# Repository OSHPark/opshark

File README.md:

# LAN'd Shark Project
The LAN'd Shark is a small, wifi-connected shark robot with some wicked hair and underglow lights. This was built and designed by the Oshpark team for [PDX Mini-Maker Faire](https://www.omsi.edu/maker-faire-pdx) 2015. 

The shark communicates via an MQTT server, and has supplimental remote control boards that allow a direct interface. However, you could esily modify it for automated or automatic control. If you need a remote MQTT server, [data.sparkfun.com](https://data.sparkfun.com/) is simple and easy to use, or you can install your own with tools  such as [Mosquitto](http://mosquitto.org/).

## Project Status
### [BaseStation](basestation/)
The basestation is fully operational, and capable of reading up to 3 teensies, and transmitting data over a network to an MQTT server.

### [Controller](controller/)
The controller is fully operational in both hardware and code.

### [Shark Bot](sharkbot/)
The Shark Brains hardware is fully operational, and can drive several servo motors from an ESP2866. 

The chassis mechanics are still a bit undefined, and a bit erratic. However, the base board works great as a mounting platform for servo motors, and can be laser cut

The Arduino sketch is still in a bit of a mess, but can read incoming controller data and react. However, the Animation and ServoPlus libraries have some bugs and needs to be rewritten/updated in order for the shark to react correctly.

Here's a picture of the completed Sharkbot. 

# Required Utilities
## Software
[Arduino 1.65](https://www.arduino.cc/en/Main/Software) 

[TeensyDuino](https://www.pjrc.com/teensy/td_download.html) if using the controllers

[ESP2866 Arduino](https://github.com/esp8266/Arduino) For the Sharkbot and basestation boards

[Eagle CAD](http://www.cadsoftusa.com/download-eagle/) is needed to modify the PCB files or generate gerbers. The `.BRD` files can be directly to [OSHPark.com](http://oshpark.com) for purchase without Eagle.

## Arduino Libraries
[PubSub Client](https://github.com/Imroy/pubsubclient)

[Teensy 3.1 SPI Slave library](https://github.com/soerup/Teensy-3.0-SPI-Master---Slave) for the controller boards

[Adafruit Neopixel (Teensy version)](https://github.com/PaulStoffregen/Adafruit_NeoPixel)

# Liscence 
Released currently under the [MIT License](./LICENSE.txt)

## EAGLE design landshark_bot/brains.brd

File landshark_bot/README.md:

# Shark Chassis
This set of boards houses the roving LAN'd Sharks, complete with an ESP8266-12E board for a controller. 

# Software
This code uses the [ESP8266 Arduino](https://github.com/esp8266/Arduino) platform for the codebase. It also uses the Adafruit Neopixel library, which is conveniently included with the ESP Arduino downloads.

# Hardware

A very helpful resource was this tutorial for [creating a shark in maya](http://cgi.tutsplus.com/tutorials/create-a-realistic-shark-in-maya-using-subdivision-surfaces-part-3--cg-31246), even though I only used the 2d outline.

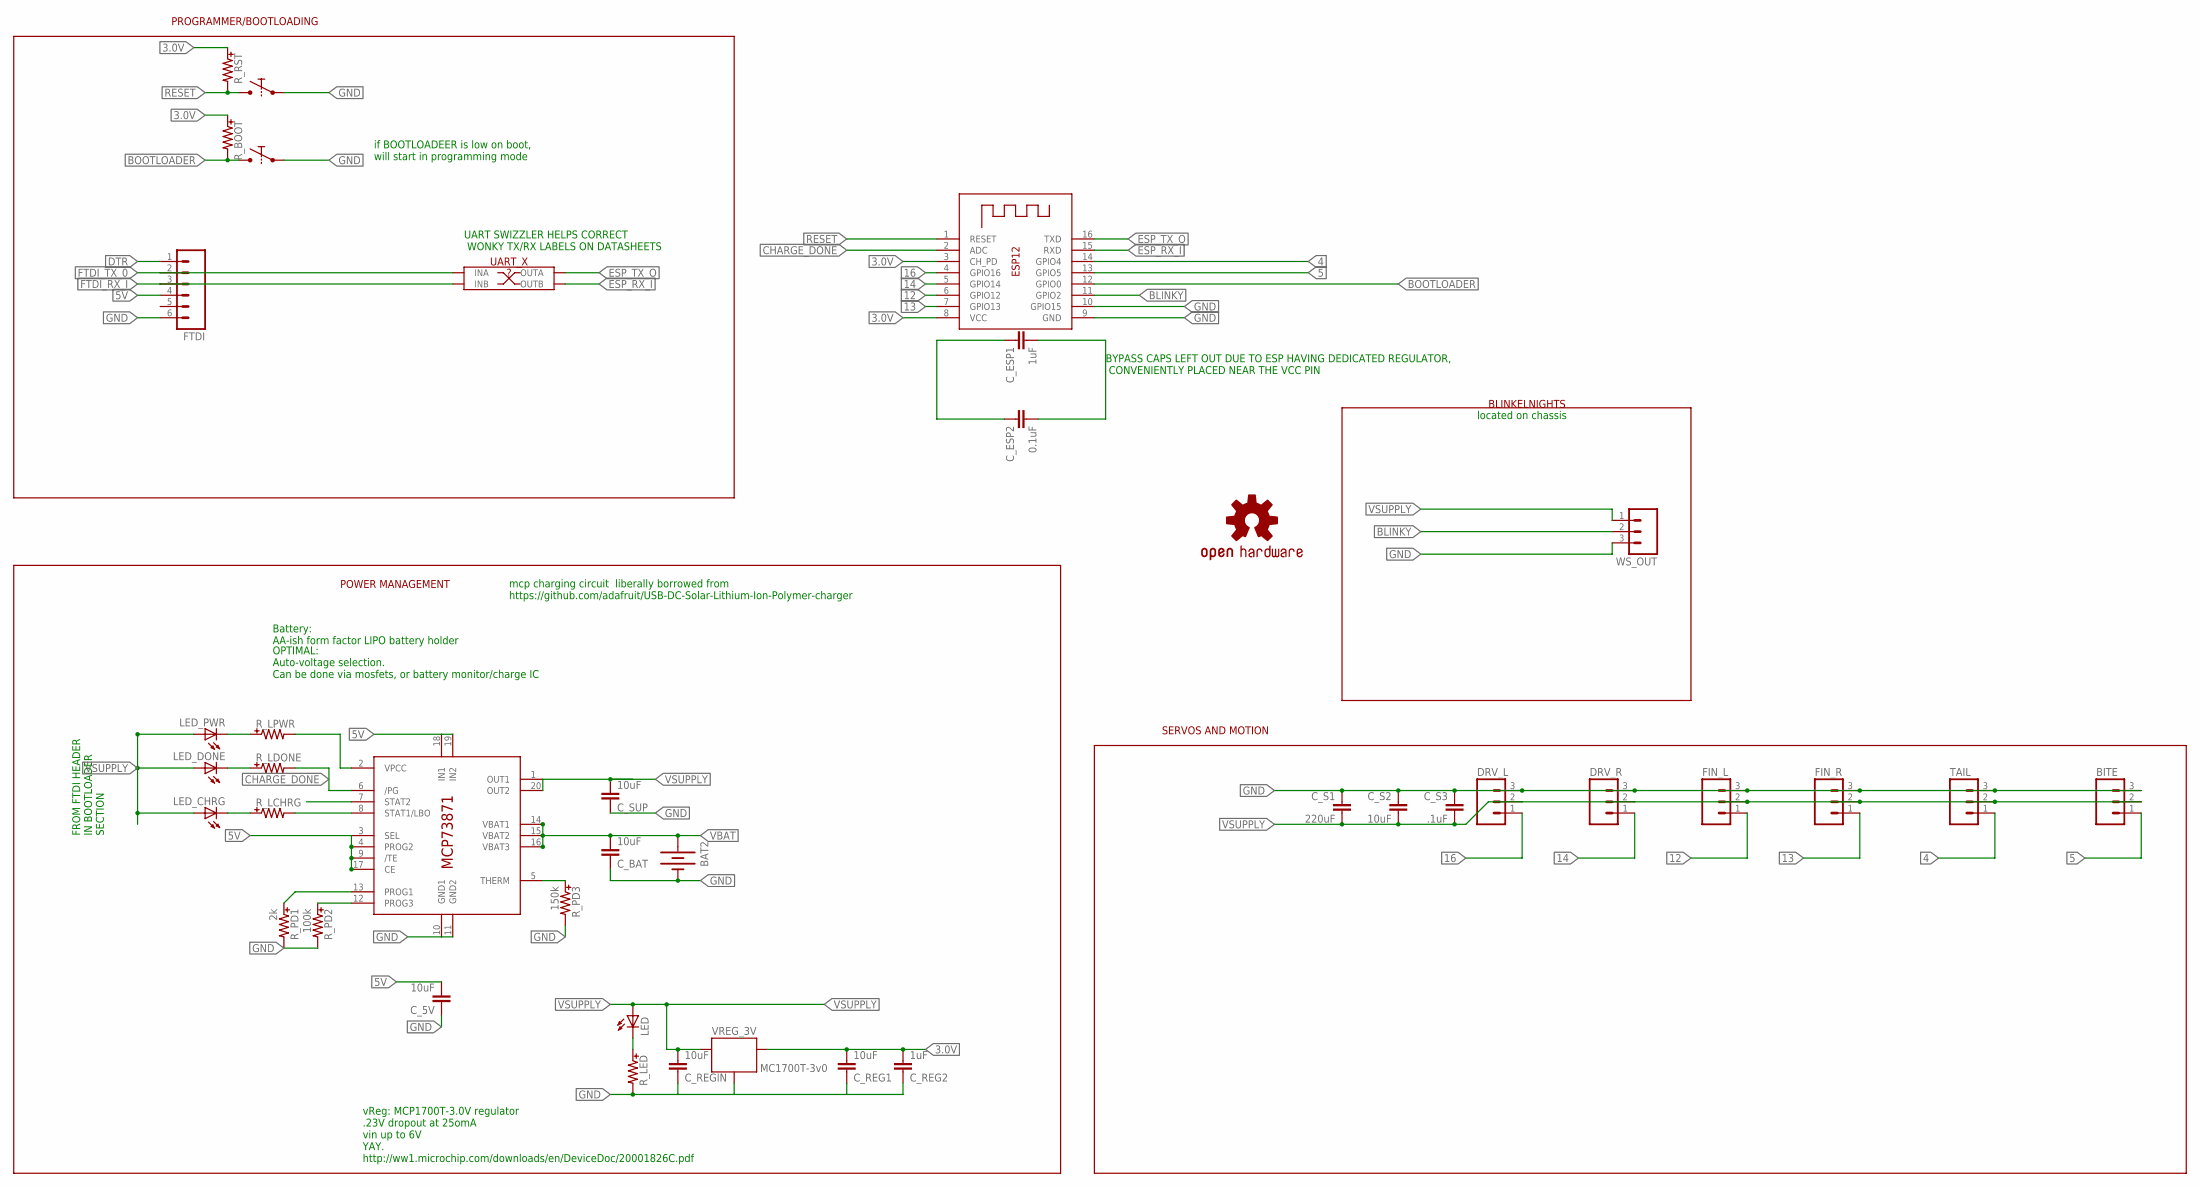
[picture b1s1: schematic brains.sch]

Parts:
BAT2: BATTERYAA; BATTERY-AA
BITE: M03LOCK; 1X03_LOCK
BTN_PROG: BUTTONPJRC; BUTTON-PJRC
BTN_RST: BUTTONPJRC; BUTTON-PJRC
C_5V: 10uF; 0402-0603-0805-UNIVERSAL
C_BAT: 10uF; 0402-0603-0805-UNIVERSAL
C_ESP1: 1uF; 0402-0603-0805-UNIVERSAL
C_ESP2: 0.1uF; 0402-0603-0805-UNIVERSAL
C_REG1: 10uF; 0402-0603-0805-UNIVERSAL
C_REG2: 1uF; 0402-0603-0805-UNIVERSAL
C_REGIN: 10uF; 0402-0603-0805-UNIVERSAL
C_S1: 220uF; 1210
C_S2: 10uF; 0402-0603-0805-UNIVERSAL
C_S3: .1uF; 0402-0603-0805-UNIVERSAL
C_SUP: 10uF; 0402-0603-0805-UNIVERSAL
DRV_L: M03LOCK; 1X03_LOCK
DRV_R: M03LOCK; 1X03_LOCK
FIN_L: M03LOCK; 1X03_LOCK
FIN_R: M03LOCK; 1X03_LOCK
FTDI: M06LOCK; 1X06_LOCK
IC_LIPO: MCP73871; QFN20
LED: LEDUNIVERSAL; 0402-0603-0805-UNIVERSAL
LED_CHRG: LEDUNIVERSAL; 0402-0603-0805-UNIVERSAL
LED_DONE: LEDUNIVERSAL; 0402-0603-0805-UNIVERSAL
LED_PWR: LEDUNIVERSAL; 0402-0603-0805-UNIVERSAL
LOGO1: OSHW-LOGOS; OSHW-LOGO-S
R_BOOT: RESISTORUNIVERSAL; 0402-0603-0805-UNIVERSAL
R_LCHRG: RESISTORUNIVERSAL; 0402-0603-0805-UNIVERSAL
R_LDONE: RESISTORUNIVERSAL; 0402-0603-0805-UNIVERSAL
R_LED: RESISTORUNIVERSAL; 0402-0603-0805-UNIVERSAL
R_LPWR: RESISTORUNIVERSAL; 0402-0603-0805-UNIVERSAL
R_PD1: 2k; 0402-0603-0805-UNIVERSAL
R_PD2: 100k; 0402-0603-0805-UNIVERSAL
R_PD3: 150k; 0402-0603-0805-UNIVERSAL
R_RST: RESISTORUNIVERSAL; 0402-0603-0805-UNIVERSAL
TAIL: M03LOCK; 1X03_LOCK
UART_X: UART_SWITCHER0603; UART_SWITCHER_0603
VREG_3V: MC1700T-3v0; SOT23
WS_OUT: M03LOCK; 1X03_LOCK
X1: ESP-12

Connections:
3.0V: C_REG1.+ (2), C_REG2.+ (2), R_BOOT.+ (1), R_RST.+ (1), VREG_3V.2 (OUT), X1.3 (CH_PD), X1.8 (VCC)
4: TAIL.1, X1.14 (GPIO4)
5: BITE.1, X1.13 (GPIO5)
5V: C_5V.+ (2), FTDI.4, IC_LIPO.3 (SEL), IC_LIPO.4 (PROG2), IC_LIPO.9 (/TE), IC_LIPO.17 (CE), IC_LIPO.18 (IN1), IC_LIPO.19 (IN2)
12: FIN_L.1, X1.6 (GPIO12)
13: FIN_R.1, X1.7 (GPIO13)
14: DRV_R.1, X1.5 (GPIO14)
16: DRV_L.1, X1.4 (GPIO16)
BLINKY: WS_OUT.2, X1.11 (GPIO2)
BOOTLOADER: BTN_PROG.A1, BTN_PROG.A2, R_BOOT.- (2), X1.12 (GPIO0)
CHARGE_DONE: IC_LIPO.6 (/PG), R_LDONE.- (2), X1.2 (ADC)
DTR: FTDI.1
ESP_RX_I: UART_X.TX_B (OUTB), X1.15 (RXD)
ESP_TX_O: UART_X.RX_B (OUTA), X1.16 (TXD)
FTDI_RX_I: FTDI.3, UART_X.RX_A (INB)
FTDI_TX_0: FTDI.2, UART_X.TX_A (INA)
GND: BAT2.GND@1 (-), BITE.3, BTN_PROG.B1, BTN_PROG.B2, BTN_RST.B1, BTN_RST.B2, C_5V.- (1), C_BAT.- (1), C_REG1.- (1), C_REG2.- (1), C_REGIN.- (1), C_S1.1, C_S2.- (1), C_S3.- (1), C_SUP.- (1), DRV_L.3, DRV_R.3, FIN_L.3, FIN_R.3, FTDI.6, IC_LIPO.10 (GND1), IC_LIPO.11 (GND2), R_LED.- (2), R_PD1.- (2), R_PD2.- (2), R_PD3.- (2), TAIL.3, VREG_3V.1 (GND), WS_OUT.3, X1.9 (GND), X1.10 (GPIO15)
unnamed: IC_LIPO.8 (STAT1/LBO), R_LCHRG.- (2)
unnamed: C_ESP1.- (1), C_ESP2.- (1)
unnamed: IC_LIPO.5 (THERM), R_PD3.+ (1)
unnamed: LED_CHRG.- (C), R_LCHRG.+ (1)
unnamed: LED.- (C), R_LED.+ (1)
unnamed: LED_DONE.- (C), R_LDONE.+ (1)
unnamed: LED_PWR.- (C), R_LPWR.+ (1)
unnamed: IC_LIPO.2 (VPCC), R_LPWR.- (2)
unnamed: C_ESP1.+ (2), C_ESP2.+ (2)
unnamed: IC_LIPO.12 (PROG3), R_PD2.+ (1)
unnamed: IC_LIPO.13 (PROG1), R_PD1.+ (1)
RESET: BTN_RST.A1, BTN_RST.A2, R_RST.- (2), X1.1 (RESET)
VBAT: BAT2.PWR@1 (+), C_BAT.+ (2), IC_LIPO.14 (VBAT1), IC_LIPO.15 (VBAT2), IC_LIPO.16 (VBAT3)
VSUPPLY: BITE.2, C_REGIN.+ (2), C_S1.2, C_S2.+ (2), C_S3.+ (2), C_SUP.+ (2), DRV_L.2, DRV_R.2, FIN_L.2, FIN_R.2, IC_LIPO.1 (OUT1), IC_LIPO.20 (OUT2), LED.+ (A), LED_CHRG.+ (A), LED_DONE.+ (A), LED_PWR.+ (A), TAIL.2, VREG_3V.3 (IN), WS_OUT.1

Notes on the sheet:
if BOOTLOADEER is low on boot, will start in programming mode
PROGRAMMER/BOOTLOADING
POWER MANAGEMENT
SERVOS AND MOTION
BLINKELNIGHTS
OPTIMAL: Auto-voltage selection. Can be done via mosfets, or battery monitor/charge IC
Battery: AA-ish form factor LIPO battery holder
UART SWIZZLER HELPS CORRECT WONKY TX/RX LABELS ON DATASHEETS
vReg: MCP1700T-3.0V regulator .23V dropout at 25omA vin up to 6V YAY. http://ww1.microchip.com/downloads/en/DeviceDoc/20001826C.pdf
mcp charging circuit liberally borrowed from https://github.com/adafruit/USB-DC-Solar-Lithium-Ion-Polymer-charger
FROM FTDI HEADER IN BOOTLOADER SECTION
located on chassis
BYPASS CAPS LEFT OUT DUE TO ESP HAVING DEDICATED REGULATOR, CONVENIENTLY PLACED NEAR THE VCC PIN

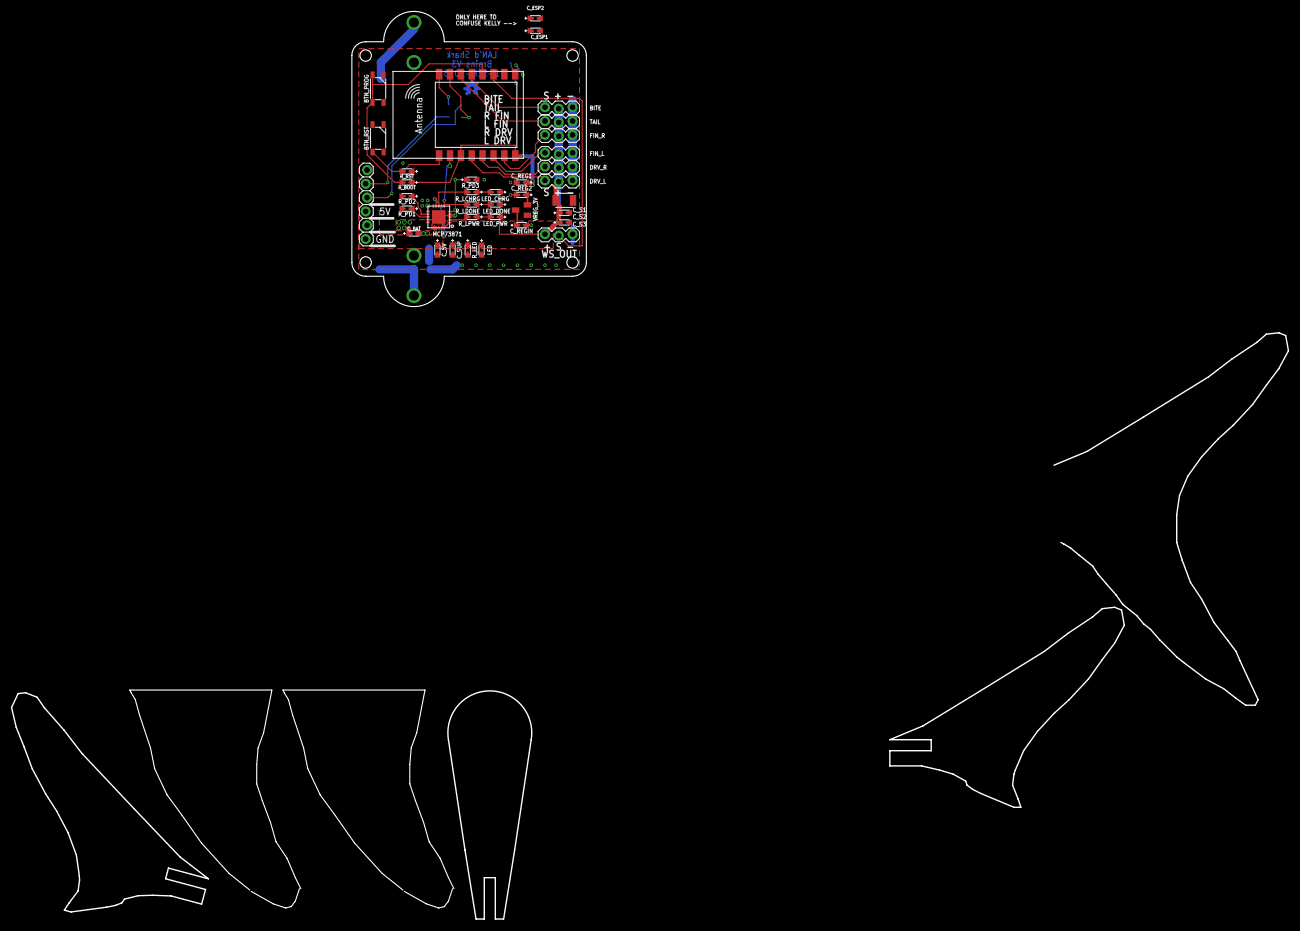
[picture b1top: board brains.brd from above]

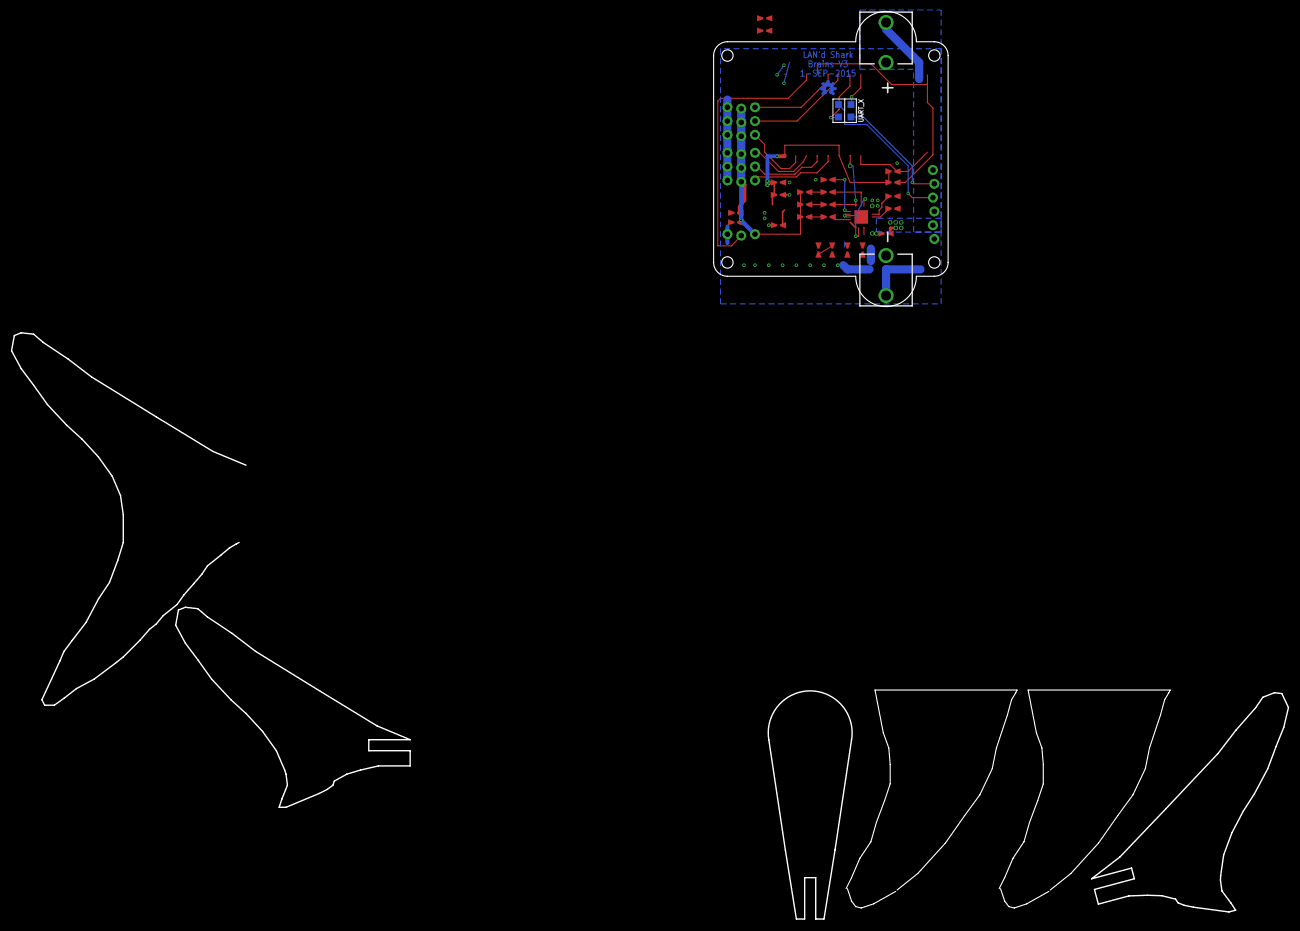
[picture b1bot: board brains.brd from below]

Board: 2 copper layers, 43.2 x 54.4 mm, 40 parts (3 on the bottom side), 30 nets.

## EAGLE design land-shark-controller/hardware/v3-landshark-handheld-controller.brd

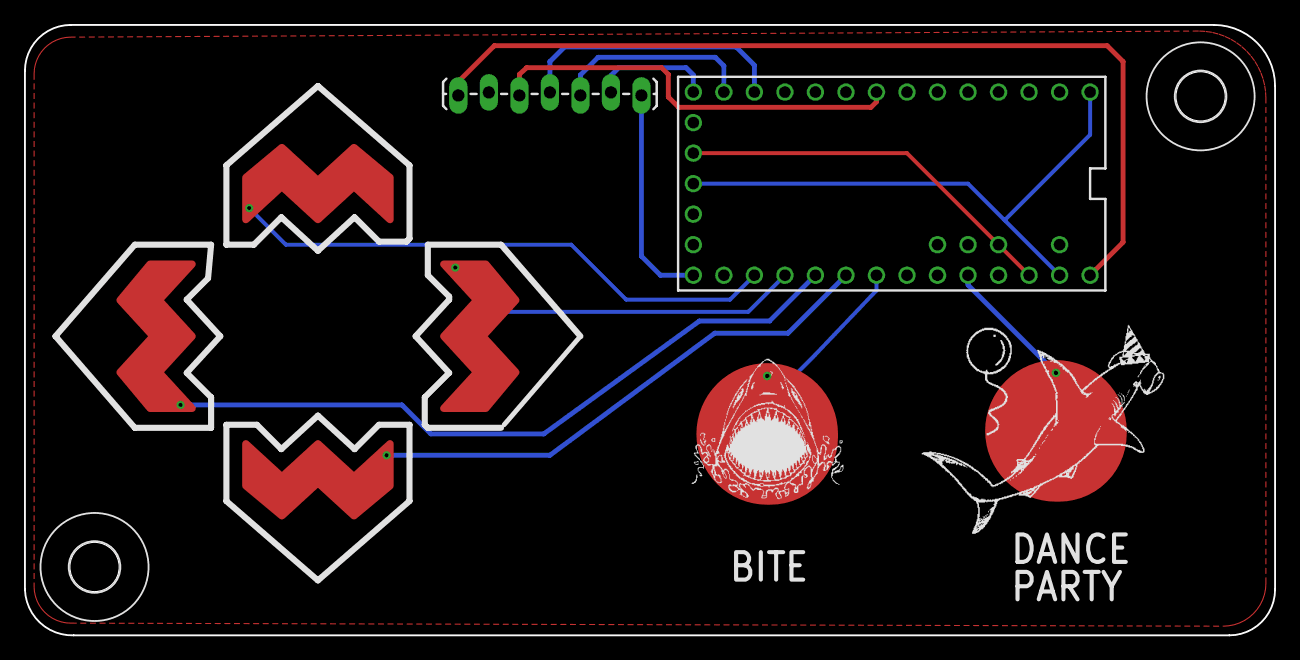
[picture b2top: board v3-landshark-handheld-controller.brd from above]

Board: 2 copper layers, 104.0 x 50.8 mm, 10 parts (0 on the bottom side), 14 nets.

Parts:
BITE: BUTTON_PASSIVE_12MM_BITE
BOTTOM: SLIDER_PASSIVE_1SEG; SLIDER_PASSIVE_1SEG_12MM
DANCE: BUTTON_PASSIVE_12MM_DANCE
H1, H2: MOUNT-HOLE4.1; 4,1
J1: BREAKOUT; 1X07_LOCK_LONGPADS
LEFT: SLIDER_PASSIVE_1SEG; SLIDER_PASSIVE_1SEG_12MM
RIGHT: SLIDER_PASSIVE_1SEG; SLIDER_PASSIVE_1SEG_12MM
TEENSY3: TEENSY_3.0+4
TOP: SLIDER_PASSIVE_1SEG; SLIDER_PASSIVE_1SEG_12MM

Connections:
3.3V: TEENSY3.3.3V, TEENSY3.3.3V1, TEENSY3.AREF
BITE: BITE.BUTTON, TEENSY3.19/A5
BOTTOM: BOTTOM.P$1, TEENSY3.18/A4
DIG_IO: J1.5, TEENSY3.6
GND: J1.6, TEENSY3.AGND, TEENSY3.GND, TEENSY3.GND1
HALT: DANCE.BUTTON, TEENSY3.22/A8
LEFT: LEFT.P$1, TEENSY3.17/A3
RIGHT: RIGHT.P$1, TEENSY3.16/A2
SPI_CS: J1.4, TEENSY3.10
SPI_DIN: J1.2, TEENSY3.12
SPI_DOUT: J1.3, TEENSY3.11
SPI_SCK: J1.1, TEENSY3.13
TOP: TEENSY3.15/A1, TOP.P$1
VIN: J1.7, TEENSY3.VIN

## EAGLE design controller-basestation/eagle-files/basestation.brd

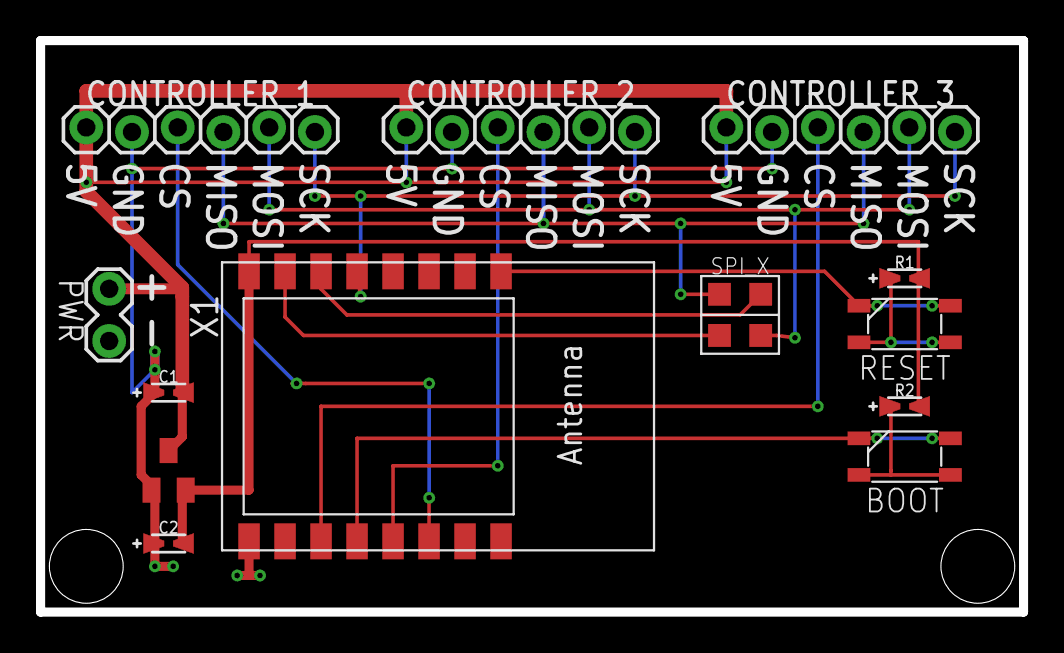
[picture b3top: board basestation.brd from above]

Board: 2 copper layers, 54.6 x 31.8 mm, 13 parts (0 on the bottom side), 15 nets.

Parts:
BOOT: BUTTONPJRC; BUTTON-PJRC
C1, C2: 0402-0603-0805-UNIVERSAL
CONTROLLER_1, CONTROLLER_2, CONTROLLER_3: 1X06_LOCK
PWR: M02LOCK; 1X02_LOCK
R1, R2: 0402-0603-0805-UNIVERSAL
RESET: BUTTONPJRC; BUTTON-PJRC
SPI_X: UART_SWITCHER0603; UART_SWITCHER_0603
U$1: VOLTAGE-REGULATORMCP1703; SOT23
X1: ESP-12

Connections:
3.3V: C2.-, R1.-, R2.-, U$1.2, X1.8
5V: C1.-, CONTROLLER_1.6, CONTROLLER_2.6, CONTROLLER_3.6, PWR.2, U$1.3
BOOT: BOOT.B1, BOOT.B2, X1.12
CTRL1: CONTROLLER_1.4, X1.14
CTRL2: CONTROLLER_2.4, X1.13
CTRL3: CONTROLLER_3.4, X1.11
GND: C1.+, C2.+, CONTROLLER_1.5, CONTROLLER_2.5, CONTROLLER_3.5, PWR.1, U$1.1, X1.9
MISO: CONTROLLER_1.3, CONTROLLER_2.3, CONTROLLER_3.3, SPI_X.RX_B
MISO-ESP: SPI_X.TX_A, X1.6
MOSI: CONTROLLER_1.2, CONTROLLER_2.2, CONTROLLER_3.2, SPI_X.TX_B
MOSI-ESP: SPI_X.RX_A, X1.7
unnamed: R1.+, RESET.A1, RESET.A2
unnamed: BOOT.A1, BOOT.A2, R2.+
RESET: RESET.B1, RESET.B2, X1.1
SCK: CONTROLLER_1.1, CONTROLLER_2.1, CONTROLLER_3.1, X1.5

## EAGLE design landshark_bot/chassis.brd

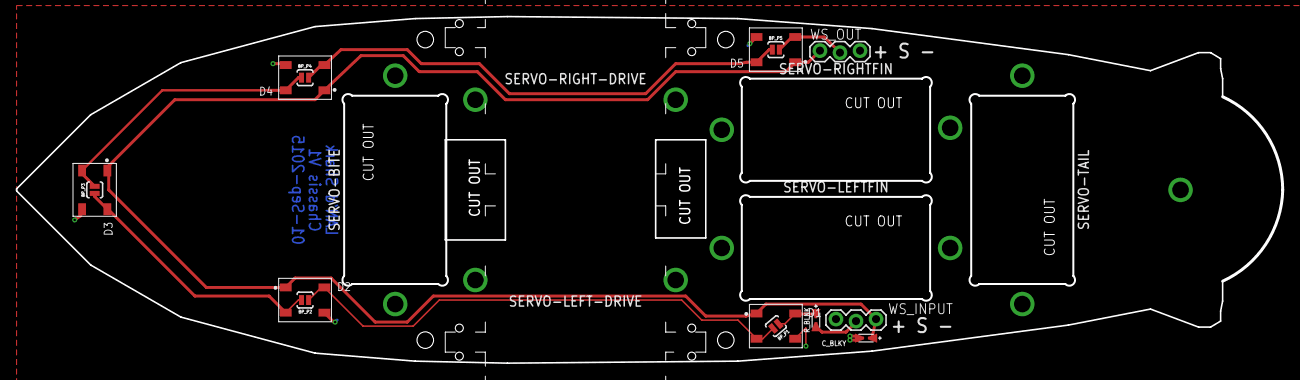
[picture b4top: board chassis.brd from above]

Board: 2 copper layers, 160.5 x 43.9 mm, 20 parts (0 on the bottom side), 9 nets.

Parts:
BP_P1, BP_P2, BP_P3, BP_P4, BP_P5: PAD-JUMPER-2-NO_YES_SILK
C_BLKY: 0.1uF; 0402-0603-0805-UNIVERSAL
D1, D2, D3, D4, D5: WS2812B
R_BLNK: 50; 0402-0603-0805-UNIVERSAL
SERVO-BITE: MICROSERVER-VERTICAL
SERVO-LEFT-DRIVE: RIGHT-DRIVE-SERVO; MICROSERVO-HORIZONTAL-FLIPPED
SERVO-LEFTFIN: MICROSERVER-VERTICAL
SERVO-RIGHT-DRIVE: MICROSERVO-HORIZONTAL
SERVO-RIGHTFIN: MICROSERVER-VERTICAL
SERVO-TAIL: MICROSERVER-VERTICAL
WS_INPUT: 1X03_LOCK
WS_OUT: 1X03_LOCK

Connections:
BLINKY: R_BLNK.-, WS_INPUT.2
GND: C_BLKY.-, D1.3, D2.3, D3.3, D4.3, D5.3, WS_INPUT.1, WS_OUT.3
unnamed: BP_P1.2, BP_P2.1, D1.2, D2.4
unnamed: BP_P4.2, BP_P5.1, D4.2, D5.4
unnamed: BP_P5.2, D5.2, WS_OUT.2
unnamed: BP_P1.1, D1.4, R_BLNK.+
unnamed: BP_P2.2, BP_P3.1, D2.2, D3.4
unnamed: BP_P3.2, BP_P4.1, D3.2, D4.4
VSUPPLY: C_BLKY.+, D1.1, D2.1, D3.1, D4.1, D5.1, WS_INPUT.3, WS_OUT.1

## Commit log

2015-08-09 V0, as built
2015-08-24 Functional MQTT messageing and base code
2015-08-24 Version 2 shark prototype boards
2015-08-24 Added code and schematics for v1 of the land shark controller.
2015-08-25 Prep for publication
2015-08-25 Skeletal code for multi-controller basestation
2015-08-25 Move for better organization
2015-08-25 Fixed silly silk. Moved trace. Changed LEFT and BOTTOM pins.
2015-08-25 Added shark images to BITE and DANCE PARTY. Board file ready for gerberizing.
2015-08-25 Made order. Added reference images. Added composite preview image. Added gerbers.
2015-08-25 Swapped pins for LEFT and DOWN for better routing.
2015-08-25 Moved traces to bottom layer. Added top ground plane with 40 mils isolation.
2015-08-26 Preleminary layout for redoing in shark form factor
2015-08-31 Added two mount holes, made board a little bigger, and added breakout power and SPI header.
2015-09-01 Added v3 gerbers, final board. Added 7-pin breakout as per feeeeture creeeeep. Use the gerbers, I took some silk off the top layer.
2015-09-01 Just renaming folders.
2015-09-01 Shark layout partly determined
2015-09-01 Clean names for splitting files
2015-09-01 Placement and LED routing complete
2015-09-02 Updated routing and shuffled things a bit, tail
2015-09-02 Finished rerouting the brain board!
2015-09-03 Fins mostly done, need panelizing
2015-09-06 As ordered for Maker Faire
2015-09-07 As-submitted pcb for controller-wifi basestation
2015-09-07 Functional controller class abstraction
2015-09-07 Trimmed funky files and organize
2015-09-07 Functional class breakdown of capsense-controller
2015-09-07 SPI Now returns current state of buttons
2015-09-08 Semi-working!
2015-09-08 Button presses over wifi! :D
2015-09-08 Whitespace'd
2015-09-08 Cleaned up organization a bit, cleaned filenames
2015-09-12 Bot code mostly working! Pre-MMF
2015-09-12 Fixed filename
2015-09-13 Semi-working for a MF Demo
2015-09-13 Broken for some reason aaaaugh!
2015-09-13 DETECTING BUTTONS DANCING AND DOING THINGS
2015-11-17 Fixed layer issue that caused fab problem
2015-11-17 Rename file structure for clarity
2015-11-21 Update docs
2015-11-21 Add images
2015-11-21 Add hinge to part list
2015-11-21 Fix picture link
2015-11-21 Shark gif is too big to survive in the deep ocean
2015-11-23 Update button part number

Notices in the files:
parts and their libraries:
PatternAgents-TouchWidgets: License : http://creativecommons.org/licenses/by-sa/4.0/ (Creative Commons 4.0)
PatternAgents-TouchWidgets: License : http://creativecommons.org/licenses/by-sa/3.1/ (Creative Commons 3.1)
